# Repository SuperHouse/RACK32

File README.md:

Rack32 ESP32 rack-mount controller with Ethernet
================================================

Copyright 2021 SuperHouse Automation Pty Ltd  www.superhouse.tv

A general purpose control board for rack mount projects, compatible
with the [Open eXtensible Rack System](https://oxrs.io/).

DIY rack-mount projects often require an Ethernet connection, a
status display, power regulation, and other features that are not
specific to the project.

This board fits into a rack-mount case and provides those common
features so they don't have to be recreated every time.

Features:

 * ESP32 microcontroller with WiFi.
 * 10/100Mbps Ethernet.
 * Support for both DIY (12V) PoE and 48V 802.3af PoE.
 * Pluggable terminal block for optional external DC power input.
 * Automotive-grade voltage regulator for harsh electrical environments.
 * 6-way IDC "I2C-Breakout" header for linking to other boards.
 * 8-way IDC "SPI-LCD" header for connection to an LCD.
 * USB-C connector for loading firmware.
 * Auto power source selection between USB-C, PoE, and external DC.
 * I/O header with power, 2 x I2C ports, and second hardware serial port.
 * Micro SD card slot for config files, logs, and media storage.
 * Onboard temperature sensor.
 * Header for front-panel power LED.
 * Can be built with onboard PCB antenna or external WiFi antenna.

More information:

  [www.superhouse.tv/rack32](http://www.superhouse.tv/rack32)

INSTALLATION
------------
The design is saved as an EAGLE project. EAGLE PCB design software is
available from www.cadsoftusa.com free for non-commercial use. To use
this project download it and place the directory containing these files
into the "eagle" directory on your computer. Then open EAGLE and
navigate to the project.

CREDITS
-------
Designed by Jonathan Oxer jon@oxer.com.au

DISTRIBUTION
------------
The specific terms of distribution of this project are governed by the
license referenced below.

LICENSE
-------
Licensed under the TAPR Open Hardware License (www.tapr.org/OHL).
The "license" folder within this repository also contains a copy of
this license in plain text format.

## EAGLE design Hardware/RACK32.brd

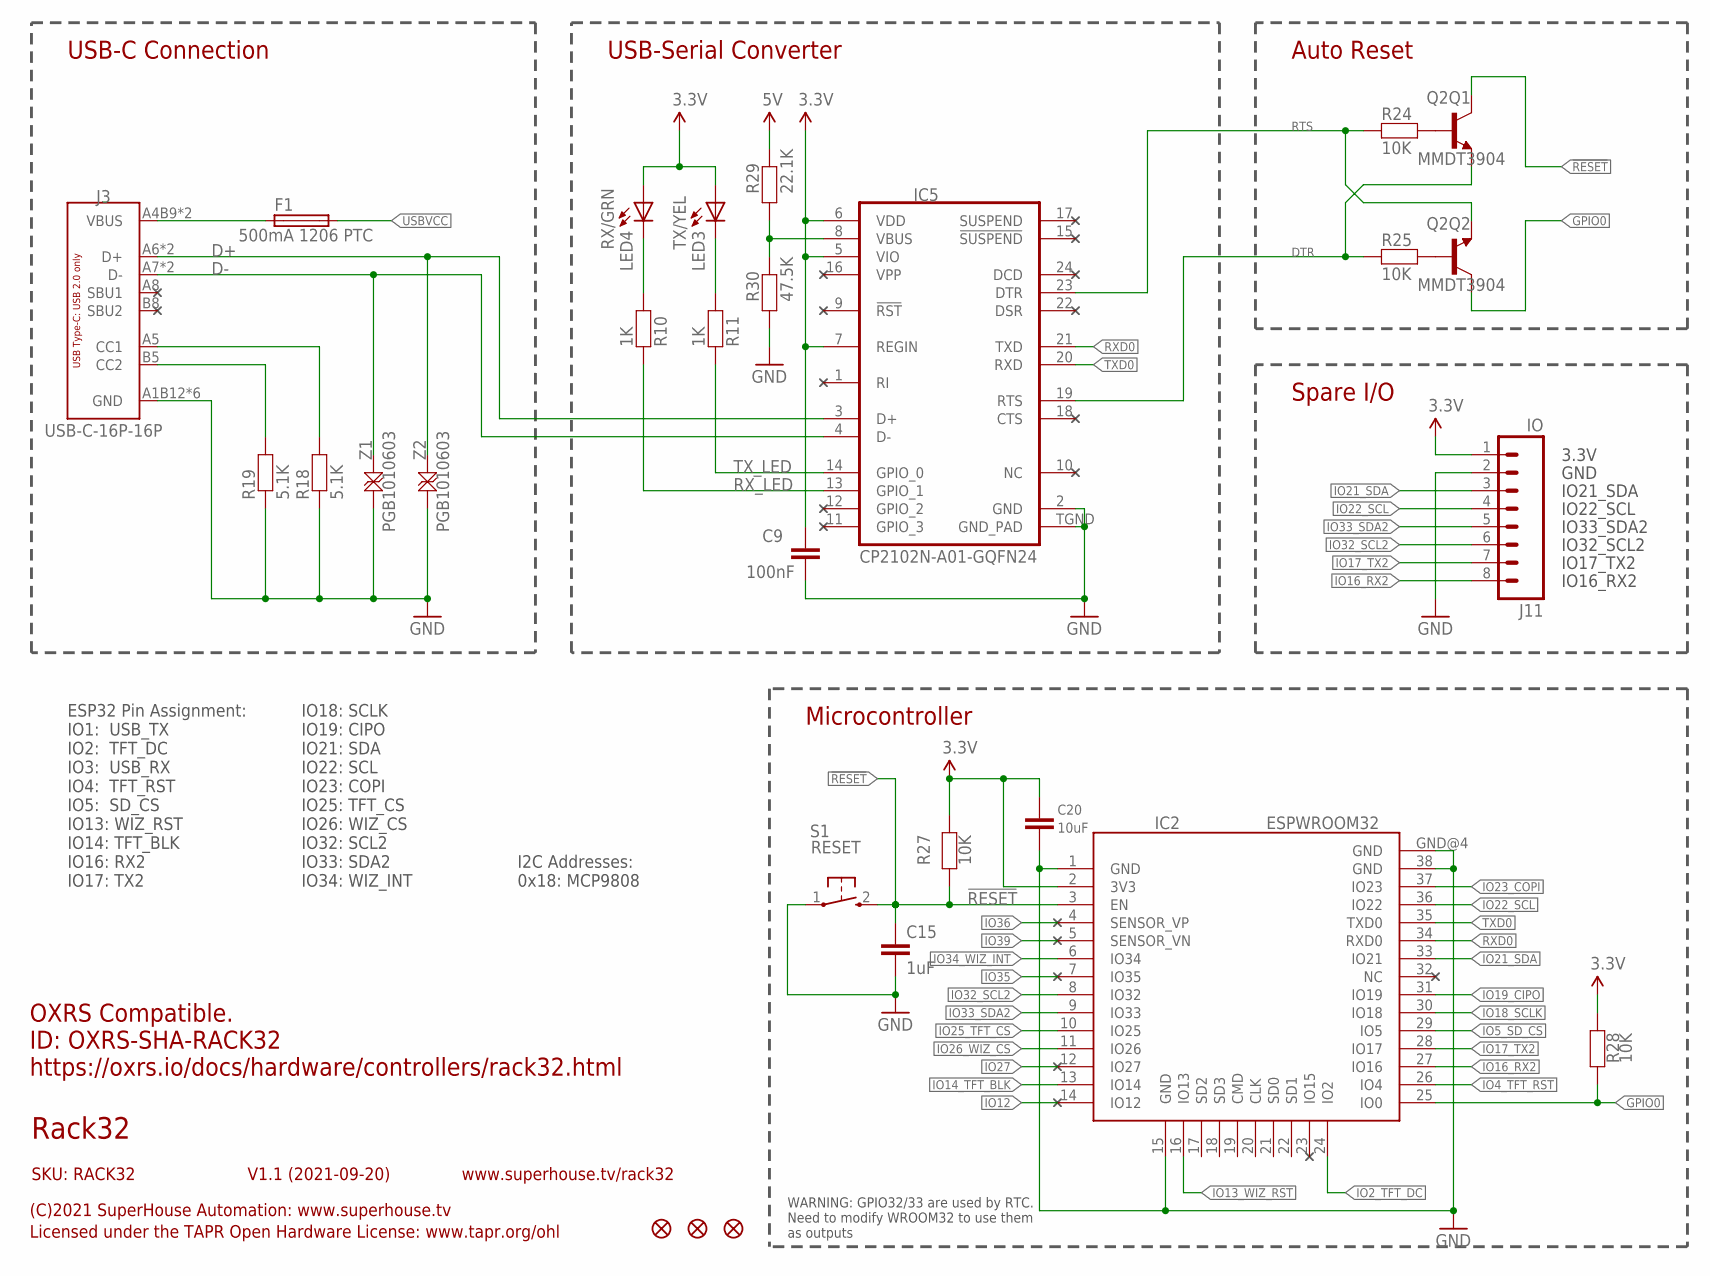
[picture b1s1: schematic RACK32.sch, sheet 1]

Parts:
C9: 100nF; C0603
C15: 1uF; C0603
C20: 10uF; C0805
F1: 500mA 1206 PTC; 1206
FID1, FID2, FID3: FIDUCIAL1X2.5; FIDUCIAL-1X2.5
IC2: ESPWROOM32
IC5: CP2102N-A01-GQFN24; QFN-24
J3: USB-C-16P-16P; USB-C-16P
J11: IO; 1X08
LED3: TX/YEL; LED-0603
LED4: RX/GRN; LED-0603
Q2: MMDT3904; SOT-363
R10, R11: 1K; R0603
R18, R19: 5.1K; R0603
R24, R25, R27, R28: 10K; R0603
R29: 22.1K; R0603
R30: 47.5K; R0603
S1: RESET; TACTILE_SMT_3X4X2
Z1, Z2: PGB1010603; TVS0603

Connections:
3.3V: C9.1, C20.1, IC2.2 (3V3), IC5.5 (VIO), IC5.6 (VDD), IC5.7 (REGIN), J11.1, LED3.A, LED4.A, R27.1, R28.1; also elsewhere on the board
5V: R29.2; also elsewhere on the board
!RESET: C15.1, IC2.3 (EN), Q2.3 (C), R27.2, S1.2 (S); also elsewhere on the board
D+: IC5.3 (D+), J3.A6 (D+), J3.B6 (D+), Z2.2
D-: IC5.4 (D-), J3.A7 (D-), J3.B7 (D-), Z1.2
DTR: IC5.23 (DTR), Q2.1 (E), R24.1
GND: C9.2, C15.2, C20.2, IC2.1 (GND), IC2.15 (GND), IC2.38 (GND), IC2.GND@4 (GND), IC5.2 (GND), IC5.TGND (GND_PAD), J3.A1B12 (GND), J3.A12B1 (GND), J3.FIX1 (GND), J3.FIX2 (GND), J3.FIX3 (GND), J3.FIX4 (GND), J11.2, R18.1, R19.1, R30.1, S1.1, Z1.1, Z2.1; also elsewhere on the board
GPIO0: IC2.25 (IO0), Q2.6 (C), R28.2
IO2_TFT_DC: IC2.24 (IO2); also elsewhere on the board
IO4_TFT_RST: IC2.26 (IO4); also elsewhere on the board
IO5_SD_CS: IC2.29 (IO5); also elsewhere on the board
IO12: IC2.14 (IO12)
IO13_WIZ_RST: IC2.16 (IO13); also elsewhere on the board
IO14_TFT_BLK: IC2.13 (IO14); also elsewhere on the board
IO16_RX2: IC2.27 (IO16), J11.8
IO17_TX2: IC2.28 (IO17), J11.7
IO18_SCLK: IC2.30 (IO18); also elsewhere on the board
IO19_CIPO: IC2.31 (IO19); also elsewhere on the board
IO21_SDA: IC2.33 (IO21), J11.3; also elsewhere on the board
IO22_SCL: IC2.36 (IO22), J11.4; also elsewhere on the board
IO23_COPI: IC2.37 (IO23); also elsewhere on the board
IO25_TFT_CS: IC2.10 (IO25); also elsewhere on the board
IO26_WIZ_CS: IC2.11 (IO26); also elsewhere on the board
IO27: IC2.12 (IO27)
IO32_SCL2: IC2.8 (IO32), J11.6
IO33_SDA2: IC2.9 (IO33), J11.5
IO34_WIZ_INT: IC2.6 (IO34); also elsewhere on the board
IO35: IC2.7 (IO35)
IO36: IC2.4 (SENSOR_VP)
IO39: IC2.5 (SENSOR_VN)
unnamed: Q2.2 (B), R25.2
unnamed: J3.B5 (CC2), R19.2
unnamed: J3.A5 (CC1), R18.2
unnamed: Q2.5 (B), R24.2
unnamed: LED3.C, R11.2
unnamed: LED4.C, R10.2
unnamed: IC5.8 (VBUS), R29.1, R30.2
RTS: IC5.19 (RTS), Q2.4 (E), R25.1
RXD0: IC2.34 (RXD0), IC5.21 (TXD)
RX_LED: IC5.13 (GPIO_1), R10.1
TXD0: IC2.35 (TXD0), IC5.20 (RXD)
TX_LED: IC5.14 (GPIO_0), R11.1
USBVCC: F1.2; also elsewhere on the board
USBVIN: F1.1, J3.A4B9 (VBUS), J3.A9B4 (VBUS)

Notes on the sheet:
USB-C Connection
USB-Serial Converter
Auto Reset
Microcontroller
WARNING: GPIO32/33 are used by RTC. Need to modify WROOM32 to use them as outputs
I2C Addresses: 0x18: MCP9808
ESP32 Pin Assignment: IO1: USB_TX IO2: TFT_DC IO3: USB_RX IO4: TFT_RST IO5: SD_CS IO13: WIZ_RST IO14: TFT_BLK IO16: RX2 IO17: TX2
Rack32
SKU: RACK32
(C)2021 SuperHouse Automation: www.superhouse.tv
Licensed under the TAPR Open Hardware License: www.tapr.org/ohl
www.superhouse.tv/rack32
V1.1 (2021-09-20)
Spare I/O
3.3V
GND
IO21_SDA
IO22_SCL
IO33_SDA2
IO32_SCL2
IO17_TX2
IO16_RX2
OXRS Compatible. ID: OXRS-SHA-RACK32 https://oxrs.io/docs/hardware/controllers/rack32.html
IO18: SCLK IO19: CIPO IO21: SDA IO22: SCL IO23: COPI IO25: TFT_CS IO26: WIZ_CS IO32: SCL2 IO33: SDA2 IO34: WIZ_INT

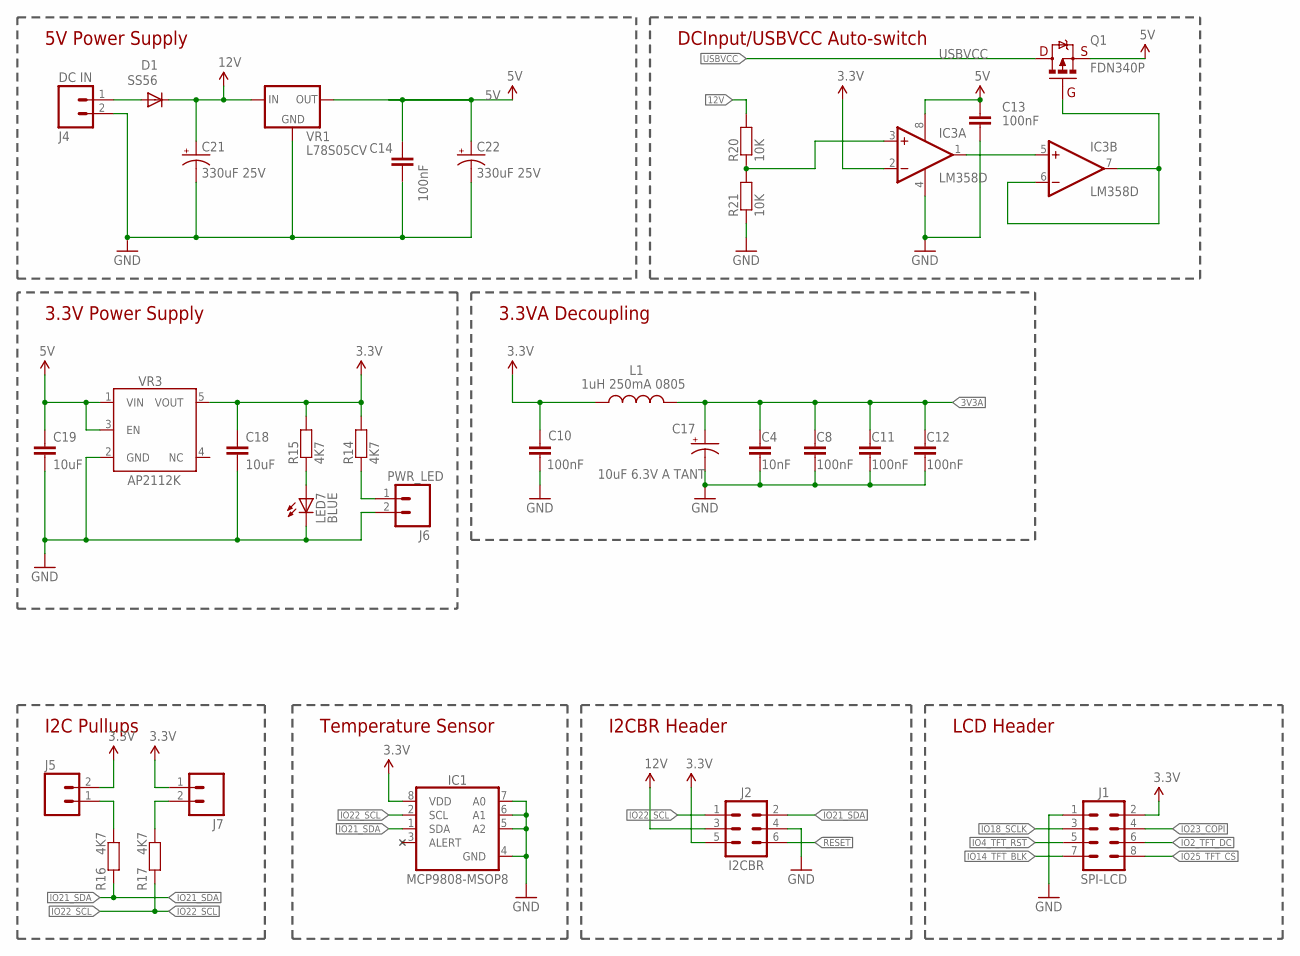
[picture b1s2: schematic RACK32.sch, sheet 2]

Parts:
C4: 10nF; C0603
C8, C10, C11, C12, C13, C14: 100nF; C0603
C17: 10uF 6.3V A TANT; EIA3216
C18, C19: 10uF; C0805
C21, C22: 330uF 25V; PANASONIC_G
D1: SS56; SMA-DIODE
IC1: MCP9808-MSOP8; MSOP-8
IC3: LM358D; SO08
J1: SPI-LCD; 2X04-2.54-SHROUDED
J2: I2CBR; 2X3-2.54-SHROUDED
J4: DC IN; SCREWTERMINAL-3.81MM-HOR-2
J5, J7: M02-PIN-JUMP-Y; 1X02-P-JUMP-Y
J6: PWR_LED; 1X02-P
L1: 1uH 250mA 0805; L2012C
LED7: BLUE; LED-0603
Q1: FDN340P; SOT23-3
R14, R15, R16, R17: 4K7; R0603
R20, R21: 10K; R0603
VR1: L78S05CV; TO220
VR3: AP2112KSOT25; SOT23-5

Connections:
3.3V: C10.1, C18.1, IC1.8 (VDD), IC3.2 (-IN), J1.2, J2.5, J5.2, J7.1, L1.1, R14.2, R15.2, VR3.5 (VOUT); also elsewhere on the board
3V3A: C4.1, C8.1, C11.1, C12.1, C17.A (+), L1.2; also elsewhere on the board
5V: C13.1, C14.1, C19.1, C22.+, IC3.8 (V+), Q1.2 (S), VR1.3 (OUT), VR3.1 (VIN), VR3.3 (EN); also elsewhere on the board
12V: C21.+, D1.C, J2.3, R20.2, VR1.1 (IN); also elsewhere on the board
!RESET: J2.6; also elsewhere on the board
GND: C4.2, C8.2, C10.2, C11.2, C12.2, C13.2, C14.2, C17.C (-), C18.2, C19.2, C21.-, C22.-, IC1.4 (GND), IC1.5 (A2), IC1.6 (A1), IC1.7 (A0), IC3.4 (V-), J1.1, J2.4, J4.2, J6.2, LED7.C, R21.1, VR1.2 (GND), VR1.HEATSINK (GND), VR1.TAB (GND), VR3.2 (GND); also elsewhere on the board
IO2_TFT_DC: J1.6; also elsewhere on the board
IO4_TFT_RST: J1.5; also elsewhere on the board
IO14_TFT_BLK: J1.7; also elsewhere on the board
IO18_SCLK: J1.3; also elsewhere on the board
IO21_SDA: IC1.1 (SDA), J2.2, R16.2; also elsewhere on the board
IO22_SCL: IC1.2 (SCL), J2.1, R17.2; also elsewhere on the board
IO23_COPI: J1.4; also elsewhere on the board
IO25_TFT_CS: J1.8; also elsewhere on the board
unnamed: LED7.A, R15.1
unnamed: J6.1, R14.1
unnamed: J5.1, R16.1
unnamed: J7.2, R17.1
unnamed: IC3.3 (+IN), R20.1, R21.2
unnamed: IC3.6 (-IN), IC3.7 (OUT), Q1.1 (G)
unnamed: IC3.1 (OUT), IC3.5 (+IN)
unnamed: D1.A, J4.1
USBVCC: Q1.3 (D); also elsewhere on the board

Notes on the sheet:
5V Power Supply
DCInput/USBVCC Auto-switch
3.3VA Decoupling
3.3V Power Supply
LCD Header
I2CBR Header
Temperature Sensor
I2C Pullups

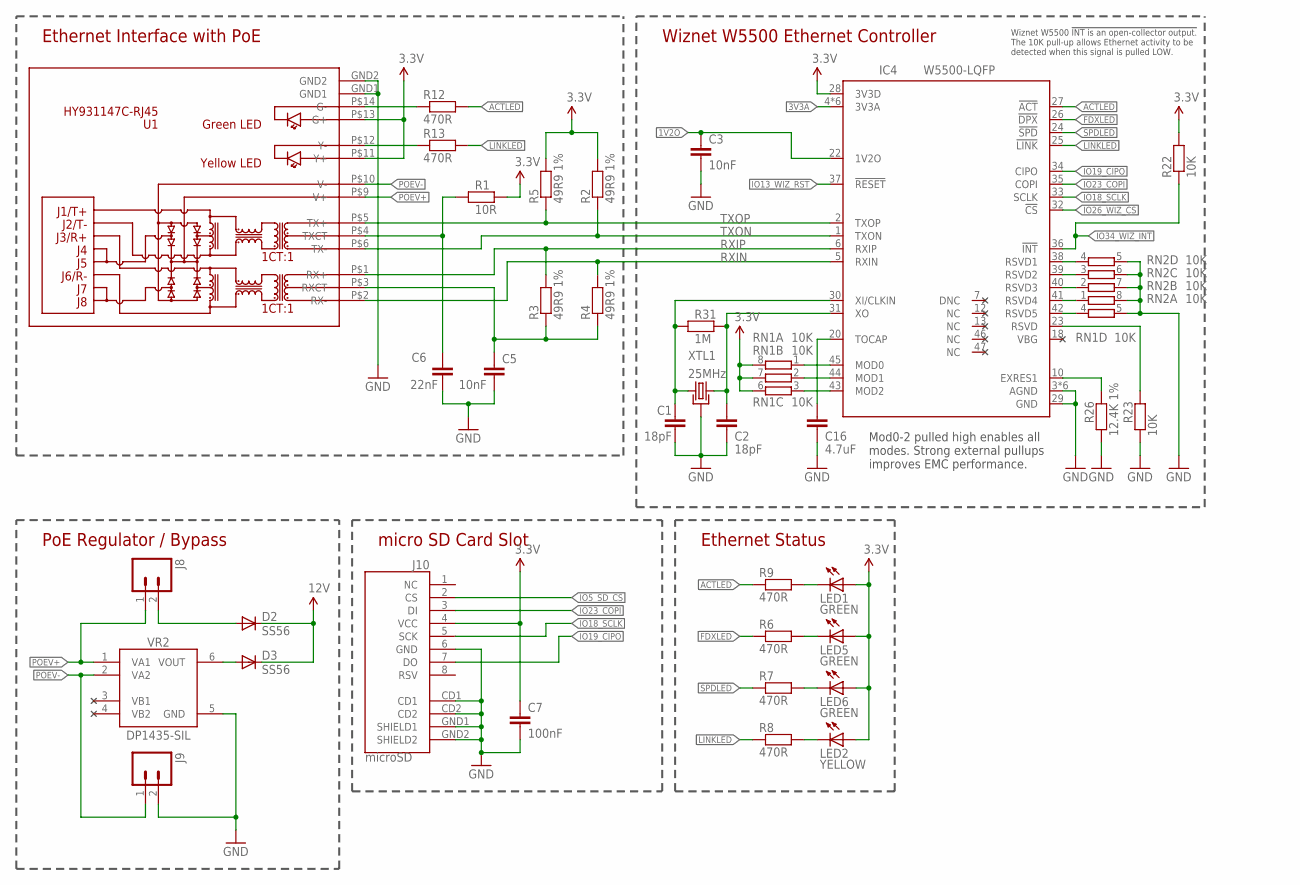
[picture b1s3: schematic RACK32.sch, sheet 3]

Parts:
C1, C2: 18pF; C0603
C3, C5: 10nF; C0603
C6: 22nF; C0603
C7: 100nF; C0603
C16: 4.7uF; C0603
D2, D3: SS56; SMA-DIODE
IC4: W5500-LQFP; LQFP48
J8, J9: M02-PIN-JUMP-Y; 1X02-P-JUMP-Y
J10: microSD; MICRO-SD-SOCKET-PP
LED1, LED5, LED6: GREEN; LED-0603
LED2: YELLOW; LED-0603
R1: 10R; R0603
R2, R3, R4, R5: 49R9 1%; R0603
R6, R7, R8, R9, R12, R13: 470R; R0603
R22, R23: 10K; R0603
R26: 12.4K 1%; R0603
R31: 1M; R0603
RN1, RN2: 10K; CAY16
U1: HY931147C-RJ45; HY931147C
VR2: DP1435-SIL; DP1435
XTL1: 25MHz; CRYSTAL-SMD-3X2

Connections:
1V2O: C3.1, IC4.22 (1V2O)
3.3V: C7.1, IC4.28 (3V3D), J10.4 (VCC), LED1.A, LED2.A, LED5.A, LED6.A, R1.1, R2.2, R5.2, R22.2, RN1.6 (2), RN1.7 (2), RN1.8 (2), U1.P$11 (Y+), U1.P$13 (G+); also elsewhere on the board
3V3A: IC4.4 (3V3A), IC4.8 (3V3A), IC4.11 (3V3A), IC4.15 (3V3A), IC4.17 (3V3A), IC4.21 (3V3A); also elsewhere on the board
12V: D2.C, D3.C; also elsewhere on the board
ACTLED: IC4.27 (!ACT), R9.1, R12.2
FDXLED: IC4.26 (!DPX), R6.1
GND: C1.2, C2.2, C3.2, C5.2, C6.2, C7.2, C16.2, IC4.3 (AGND), IC4.9 (AGND), IC4.14 (AGND), IC4.16 (AGND), IC4.19 (AGND), IC4.29 (GND), IC4.48 (AGND), J9.2, J10.6 (GND), J10.CD1, J10.CD2, J10.GND1 (SHIELD1), J10.GND2 (SHIELD2), R23.2, R26.2, RN1.5 (2), RN2.5 (2), RN2.6 (2), RN2.7 (2), RN2.8 (2), U1.GND1, U1.GND2, VR2.5 (GND), XTL1.2 (GND), XTL1.4 (GND); also elsewhere on the board
IO5_SD_CS: J10.2 (CS); also elsewhere on the board
IO13_WIZ_RST: IC4.37 (!RESET); also elsewhere on the board
IO18_SCLK: IC4.33 (SCLK), J10.5 (SCK); also elsewhere on the board
IO19_CIPO: IC4.34 (CIPO), J10.7 (DO); also elsewhere on the board
IO23_COPI: IC4.35 (COPI), J10.3 (DI); also elsewhere on the board
IO26_WIZ_CS: IC4.32 (!CS); also elsewhere on the board
IO34_WIZ_INT: IC4.36 (!INT), R22.1; also elsewhere on the board
LINKLED: IC4.25 (!LINK), R8.1, R13.2
unnamed: C5.1, R3.1, R4.1, U1.P$3 (RXCT)
unnamed: D2.A, J8.2
unnamed: C2.1, IC4.31 (XO), R31.1, XTL1.3 (2)
unnamed: D3.A, VR2.6 (VOUT)
unnamed: LED6.C, R7.2
unnamed: C1.1, IC4.30 (XI/CLKIN), R31.2, XTL1.1
unnamed: LED2.C, R8.2
unnamed: C16.1, IC4.20 (TOCAP)
unnamed: C6.1, R1.2, U1.P$4 (TXCT)
unnamed: IC4.10 (EXRES1), R26.1
unnamed: IC4.23 (RSVD), R23.1
unnamed: IC4.45 (MOD0), RN1.1
unnamed: IC4.44 (MOD1), RN1.2 (1)
unnamed: IC4.43 (MOD2), RN1.3 (1)
unnamed: IC4.42 (RSVD5), RN1.4 (1)
unnamed: IC4.41 (RSVD4), RN2.1
unnamed: IC4.40 (RSVD3), RN2.2 (1)
unnamed: IC4.39 (RSVD2), RN2.3 (1)
unnamed: IC4.38 (RSVD1), RN2.4 (1)
unnamed: R12.1, U1.P$14 (G-)
unnamed: LED5.C, R6.2
unnamed: LED1.C, R9.2
unnamed: R13.1, U1.P$12 (Y-)
POEV+: J8.1, U1.P$9 (V+), VR2.1 (VA1)
POEV-: J9.1, U1.P$10 (V-), VR2.2 (VA2)
RXIN: IC4.5 (RXIN), R4.2, U1.P$2 (RX-)
RXIP: IC4.6 (RXIP), R3.2, U1.P$1 (RX+)
SPDLED: IC4.24 (!SPD), R7.1
TXON: IC4.1 (TXON), R2.1, U1.P$6 (TX-)
TXOP: IC4.2 (TXOP), R5.1, U1.P$5 (TX+)
VB1: VR2.3 (VB1)
VB2: VR2.4 (VB2)

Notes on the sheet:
micro SD Card Slot
Ethernet Status
Ethernet Interface with PoE
Wiznet W5500 Ethernet Controller
Mod0-2 pulled high enables all modes. Strong external pullups improves EMC performance.
Wiznet W5500 !INT is an open-collector output. The 10K pull-up allows Ethernet activity to be detected when this signal is pulled LOW.
PoE Regulator / Bypass

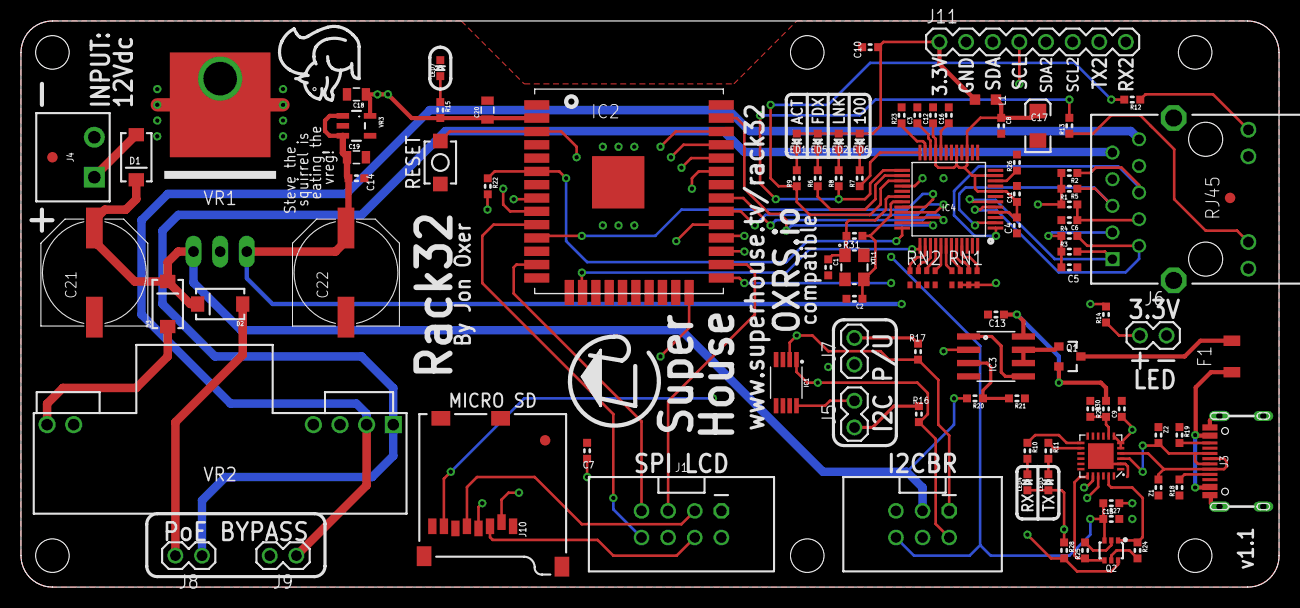
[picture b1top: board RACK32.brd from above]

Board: 4 copper layers, 120.0 x 54.0 mm, 96 parts (0 on the bottom side), 83 nets.

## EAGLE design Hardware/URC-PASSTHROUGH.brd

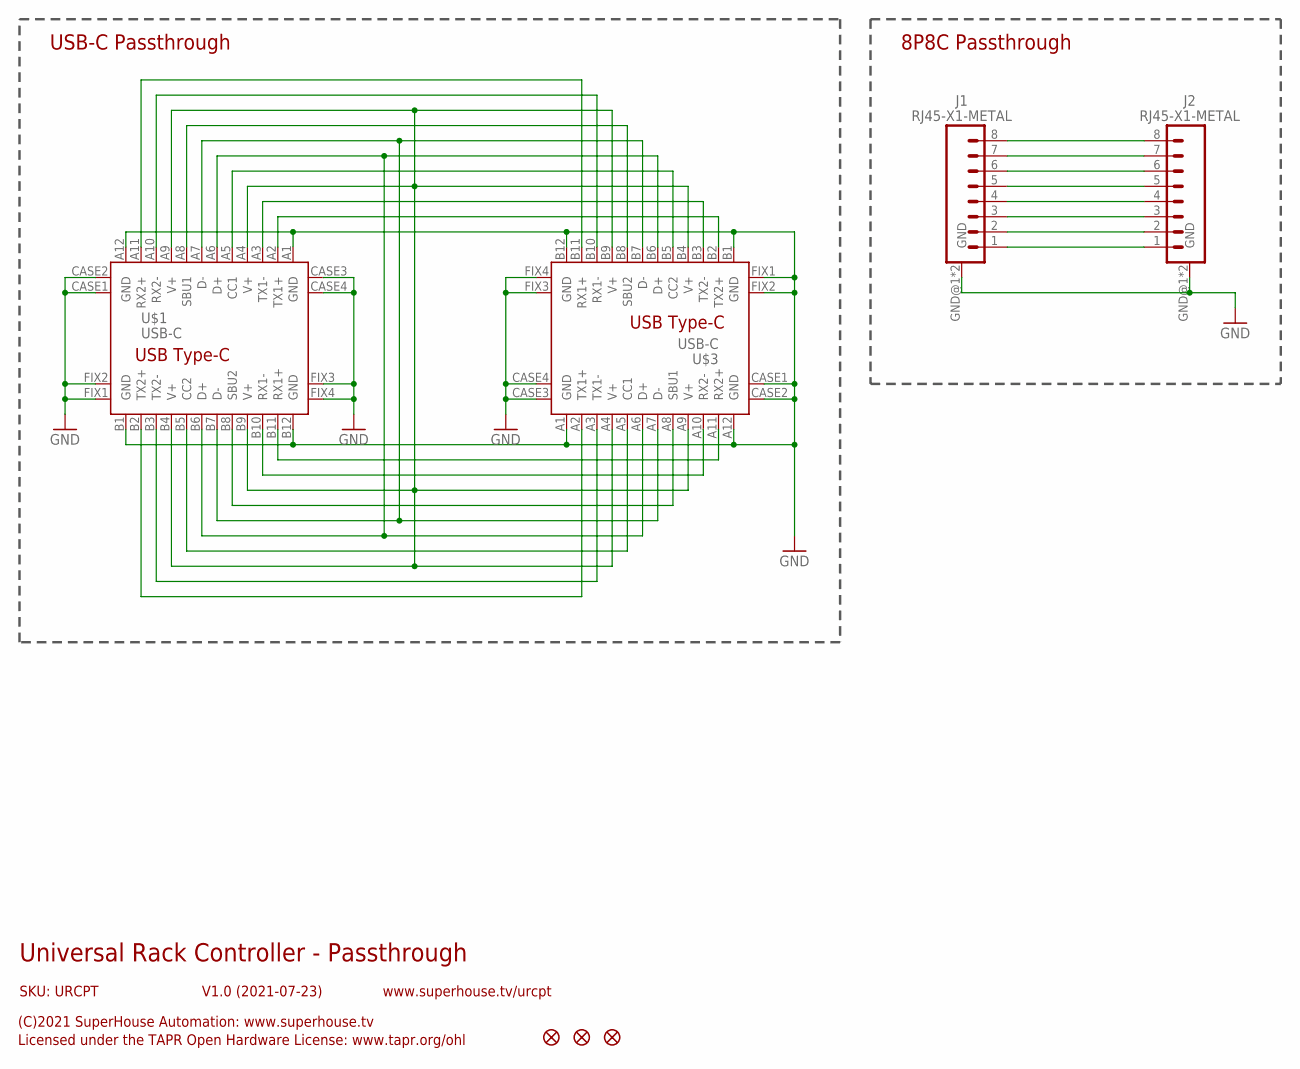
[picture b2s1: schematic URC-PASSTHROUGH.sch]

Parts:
FID1, FID2, FID3: FIDUCIAL1X2.5; FIDUCIAL-1X2.5
J1, J2: RJ45-X1-METAL; RJ45-1X1
U$1, U$3: USB-C; USB-C-U52A

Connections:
GND: J1.GND@1 (GND), J1.GND@2 (GND), J2.GND@1 (GND), J2.GND@2 (GND), U$1.A1 (GND), U$1.A12 (GND), U$1.B1 (GND), U$1.B12 (GND), U$1.CASE1 (GND), U$1.CASE2 (GND), U$1.CASE3 (GND), U$1.CASE4 (GND), U$1.FIX1 (GND), U$1.FIX2 (GND), U$1.FIX3 (GND), U$1.FIX4 (GND), U$3.A1 (GND), U$3.A12 (GND), U$3.B1 (GND), U$3.B12 (GND), U$3.CASE1 (GND), U$3.CASE2 (GND), U$3.CASE3 (GND), U$3.CASE4 (GND), U$3.FIX1 (GND), U$3.FIX2 (GND), U$3.FIX3 (GND), U$3.FIX4 (GND)
unnamed: J1.1, J2.1
unnamed: J1.2, J2.2
unnamed: J1.3, J2.3
unnamed: J1.4, J2.4
unnamed: J1.5, J2.5
unnamed: J1.6, J2.6
unnamed: J1.7, J2.7
unnamed: J1.8, J2.8
unnamed: U$1.A2 (TX1+), U$3.B2 (TX2+)
unnamed: U$1.A3 (TX1-), U$3.B3 (TX2-)
unnamed: U$1.A8 (SBU1), U$3.B8 (SBU2)
unnamed: U$1.A5 (CC1), U$3.B5 (CC2)
unnamed: U$1.A6 (D+), U$1.B6 (D+), U$3.A6 (D+), U$3.B6 (D+)
unnamed: U$1.A7 (D-), U$1.B7 (D-), U$3.A7 (D-), U$3.B7 (D-)
unnamed: U$1.A10 (RX2-), U$3.B10 (RX1-)
unnamed: U$1.A11 (RX2+), U$3.B11 (RX1+)
unnamed: U$1.B11 (RX1+), U$3.A11 (RX2+)
unnamed: U$1.B10 (RX1-), U$3.A10 (RX2-)
unnamed: U$1.A4 (V+), U$1.A9 (V+), U$1.B4 (V+), U$1.B9 (V+), U$3.A4 (V+), U$3.A9 (V+), U$3.B4 (V+), U$3.B9 (V+)
unnamed: U$1.B8 (SBU2), U$3.A8 (SBU1)
unnamed: U$1.B5 (CC2), U$3.A5 (CC1)
unnamed: U$1.B3 (TX2-), U$3.A3 (TX1-)
unnamed: U$1.B2 (TX2+), U$3.A2 (TX1+)

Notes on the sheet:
USB-C Passthrough
Universal Rack Controller - Passthrough
SKU: URCPT
(C)2021 SuperHouse Automation: www.superhouse.tv
Licensed under the TAPR Open Hardware License: www.tapr.org/ohl
www.superhouse.tv/urcpt
V1.0 (2021-07-23)
8P8C Passthrough

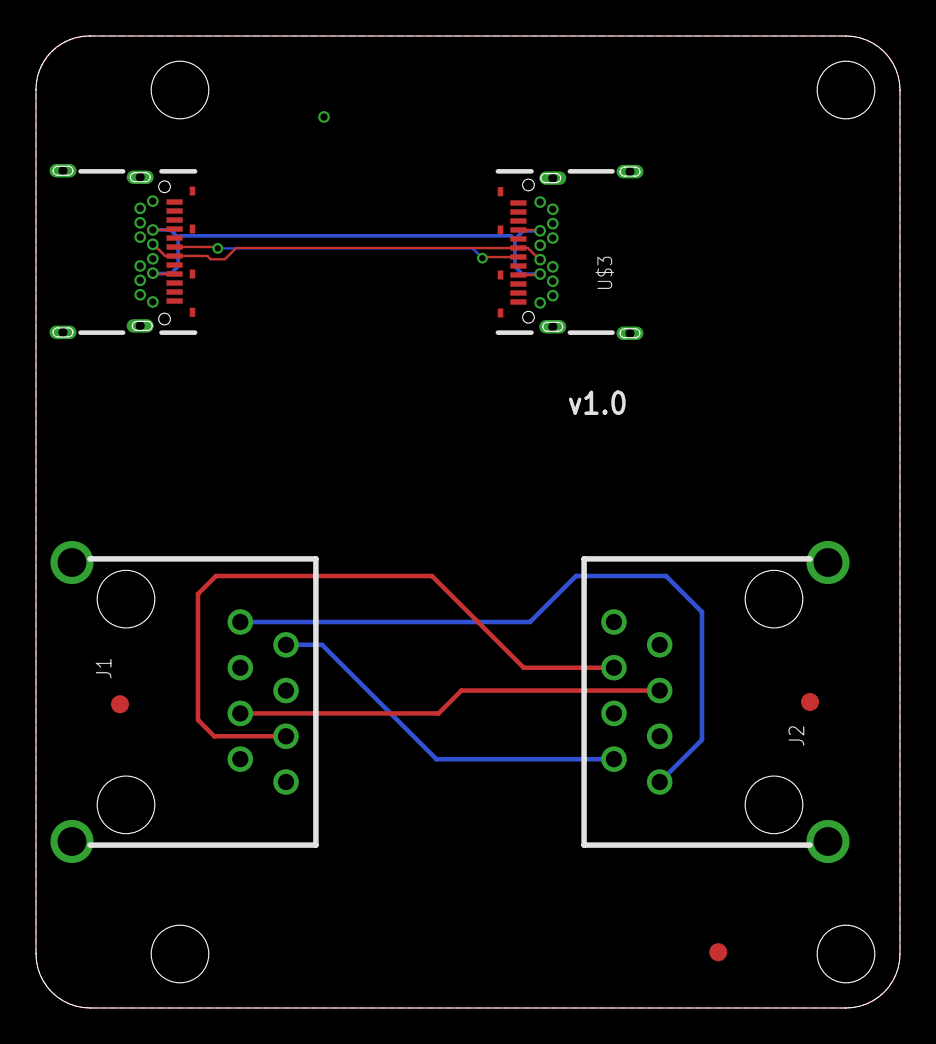
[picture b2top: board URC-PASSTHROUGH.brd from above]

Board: 4 copper layers, 48.0 x 54.0 mm, 7 parts (0 on the bottom side), 24 nets.

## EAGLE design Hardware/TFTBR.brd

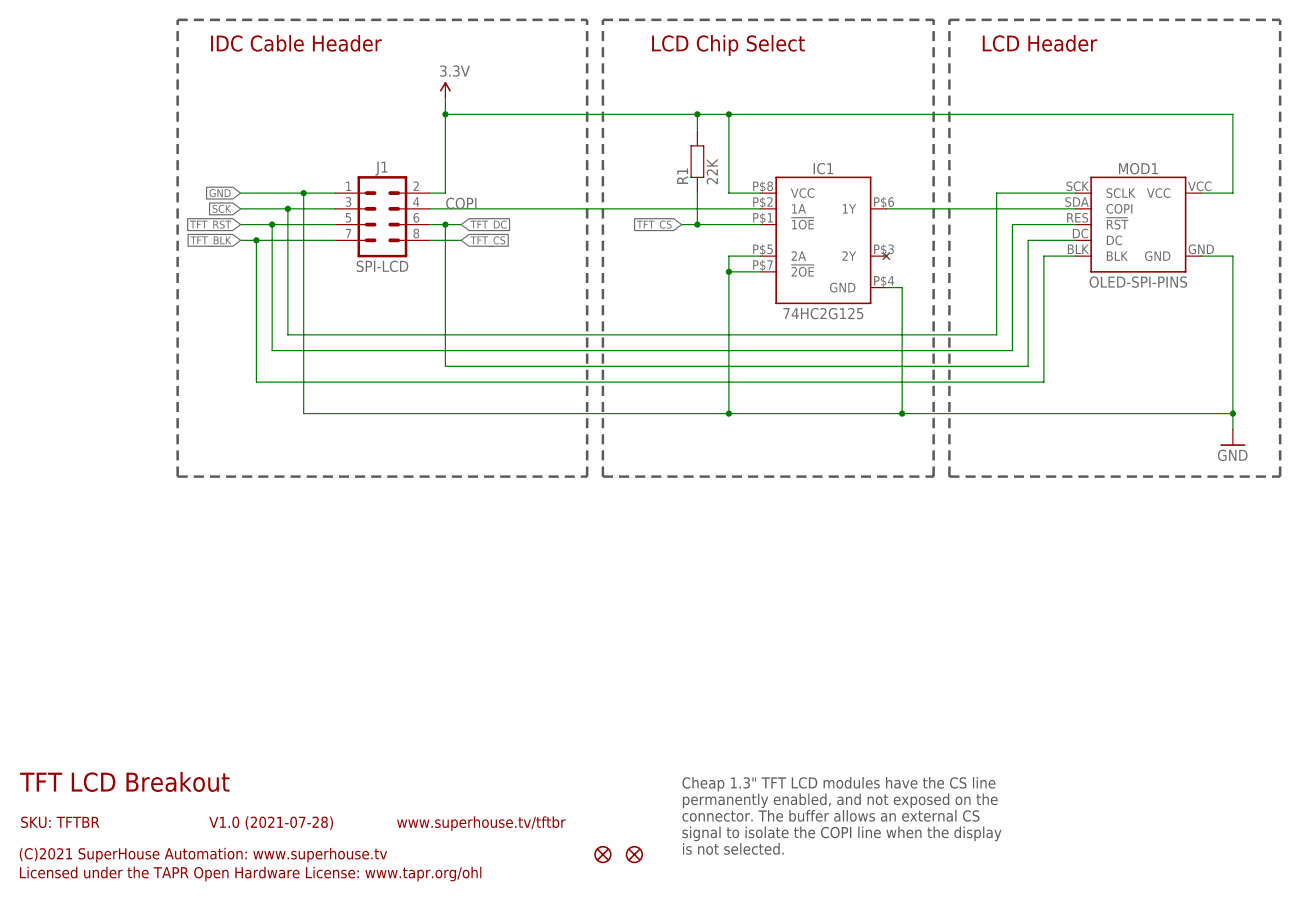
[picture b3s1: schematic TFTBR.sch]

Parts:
FID1, FID2: FIDUCIAL1X2.5; FIDUCIAL-1X2.5
IC1: 74HC2G125
J1: SPI-LCD; 2X04-2.54-SHROUDED
MOD1: OLED-SPI-PINS; OLED-240X240-1.3
R1: 22K; R0603

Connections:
3.3V: IC1.P$8 (VCC), J1.2, MOD1.VCC, R1.2
COPI: IC1.P$2 (1A), J1.4
GND: IC1.P$4 (GND), IC1.P$5 (2A), IC1.P$7 (!2OE), J1.1, MOD1.GND
unnamed: IC1.P$6 (1Y), MOD1.SDA (COPI)
SCK: J1.3, MOD1.SCK (SCLK)
TFT_BLK: J1.7, MOD1.BLK
TFT_CS: IC1.P$1 (!1OE), J1.8, R1.1
TFT_DC: J1.6, MOD1.DC
TFT_RST: J1.5, MOD1.RES (!RST)

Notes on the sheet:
TFT LCD Breakout
SKU: TFTBR
(C)2021 SuperHouse Automation: www.superhouse.tv
Licensed under the TAPR Open Hardware License: www.tapr.org/ohl
www.superhouse.tv/tftbr
V1.0 (2021-07-28)
IDC Cable Header
LCD Chip Select
LCD Header
Cheap 1.3" TFT LCD modules have the CS line permanently enabled, and not exposed on the connector. The buffer allows an external CS signal to isolate the COPI line when the display is not selected.

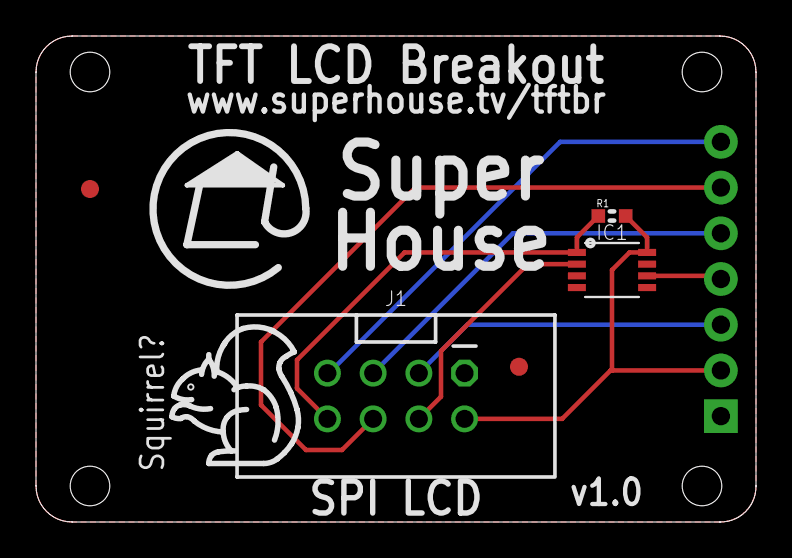
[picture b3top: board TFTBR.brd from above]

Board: 2 copper layers, 40.0 x 27.0 mm, 6 parts (1 on the bottom side), 9 nets.

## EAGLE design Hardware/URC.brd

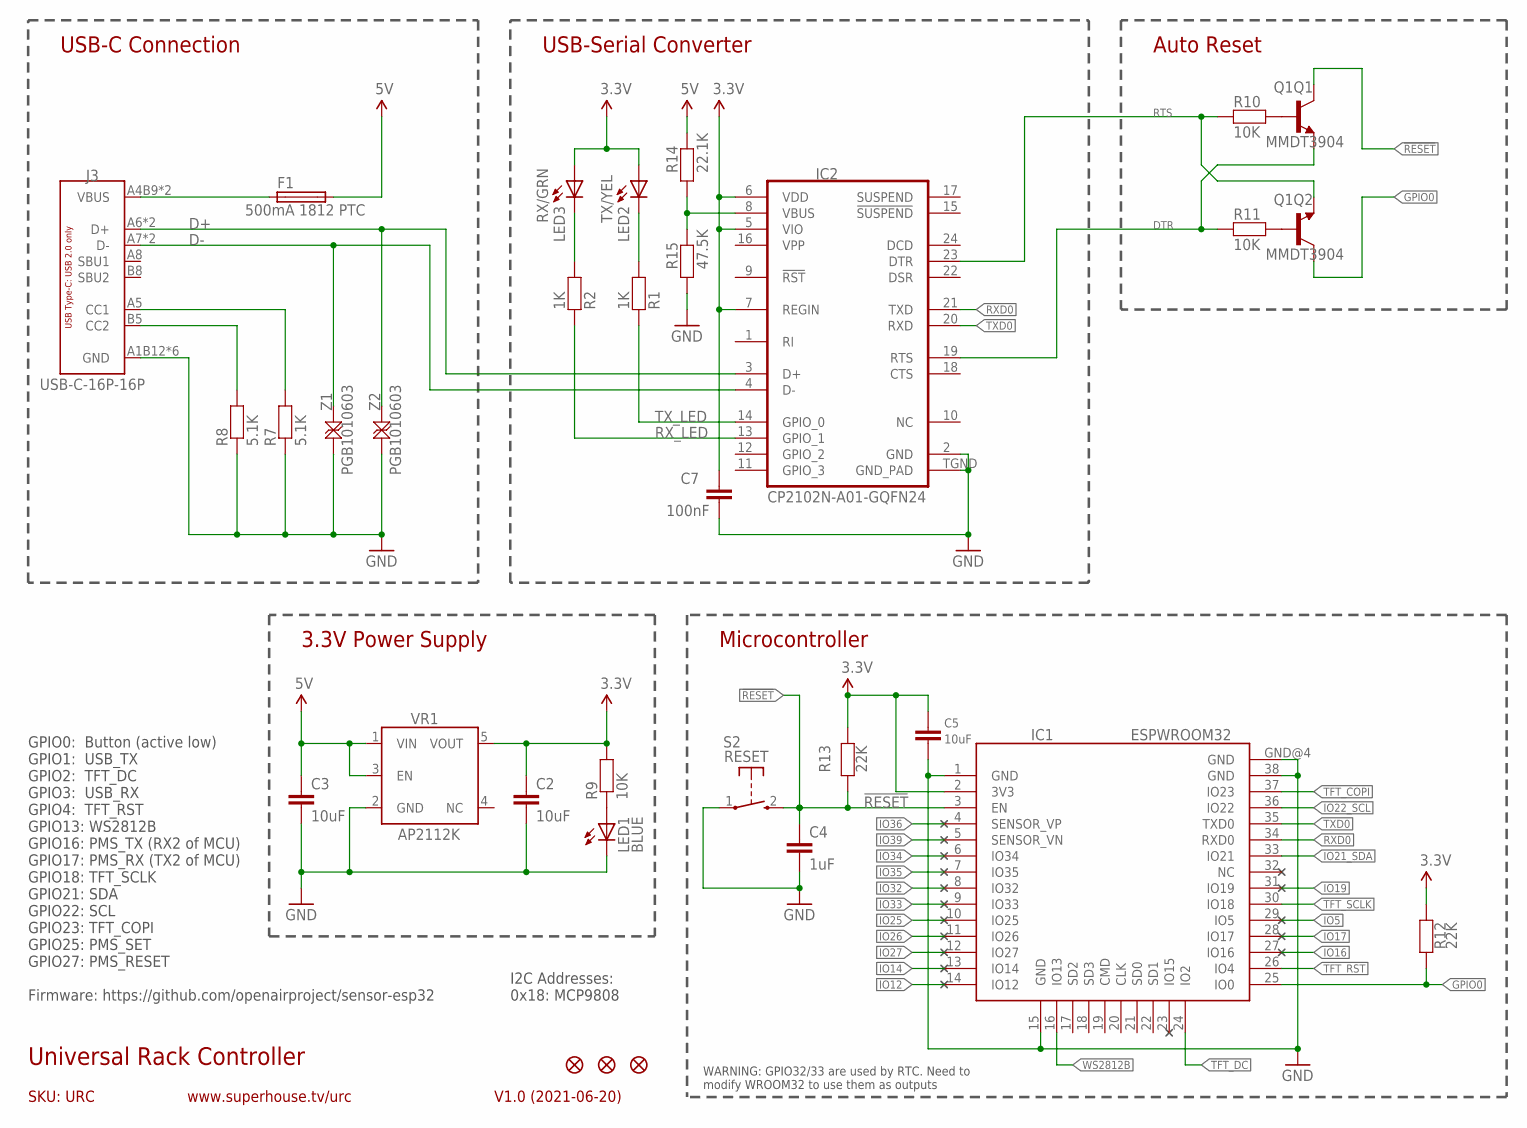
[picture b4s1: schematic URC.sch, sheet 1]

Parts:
C2, C3, C5: 10uF; C0805
C4: 1uF; C0603
C7: 100nF; C0603
F1: 500mA 1812 PTC; 1812
IC1: ESPWROOM32
IC2: CP2102N-A01-GQFN24; QFN-24
J3: USB-C-16P-16P; USB-C-16P
LED1: BLUE; LED-0603
LED2: TX/YEL; LED-0603
LED3: RX/GRN; LED-0603
Q1: MMDT3904; SOT-363
R1, R2: 1K; R0603
R7, R8: 5.1K; R0603
R9, R10, R11: 10K; R0603
R12, R13: 22K; R0603
R14: 22.1K; R0603
R15: 47.5K; R0603
S2: RESET; TACTILE_SMT_3X4X2
U$23, U$24, U$25: FIDUCIAL1X2; FIDUCIAL-1X2
VR1: AP2112KSOT25; SOT23-5
Z1, Z2: PGB1010603; TVS0603

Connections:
3.3V: C2.1, C5.1, C7.1, IC1.2 (3V3), IC2.5 (VIO), IC2.6 (VDD), IC2.7 (REGIN), LED2.A, LED3.A, R9.2, R12.1, R13.1, VR1.5 (VOUT); also elsewhere on the board
5V: C3.1, F1.2, R14.2, VR1.1 (VIN), VR1.3 (EN)
!RESET: C4.1, IC1.3 (EN), Q1.3 (C), R13.2, S2.2 (S)
D+: IC2.3 (D+), J3.A6 (D+), J3.B6 (D+), Z2.2
D-: IC2.4 (D-), J3.A7 (D-), J3.B7 (D-), Z1.2
DTR: IC2.23 (DTR), Q1.1 (E), R10.1
GND: C2.2, C3.2, C4.2, C5.2, C7.2, IC1.1 (GND), IC1.15 (GND), IC1.38 (GND), IC1.GND@4 (GND), IC2.2 (GND), IC2.TGND (GND_PAD), J3.A1B12 (GND), J3.A12B1 (GND), J3.FIX1 (GND), J3.FIX2 (GND), J3.FIX3 (GND), J3.FIX4 (GND), LED1.C, R7.1, R8.1, R15.1, S2.1, VR1.2 (GND), Z1.1, Z2.1; also elsewhere on the board
GPIO0: IC1.25 (IO0), Q1.6 (C), R12.2
IO5: IC1.29 (IO5)
IO12: IC1.14 (IO12)
IO14: IC1.13 (IO14)
IO16: IC1.27 (IO16)
IO17: IC1.28 (IO17)
IO19: IC1.31 (IO19)
IO21_SDA: IC1.33 (IO21); also elsewhere on the board
IO22_SCL: IC1.36 (IO22); also elsewhere on the board
IO25: IC1.10 (IO25)
IO26: IC1.11 (IO26)
IO27: IC1.12 (IO27)
IO32: IC1.8 (IO32)
IO33: IC1.9 (IO33)
IO34: IC1.6 (IO34)
IO35: IC1.7 (IO35)
IO36: IC1.4 (SENSOR_VP)
IO39: IC1.5 (SENSOR_VN)
unnamed: LED1.A, R9.1
unnamed: LED3.C, R2.2
unnamed: Q1.5 (B), R10.2
unnamed: Q1.2 (B), R11.2
unnamed: J3.B5 (CC2), R8.2
unnamed: J3.A5 (CC1), R7.2
unnamed: LED2.C, R1.2
unnamed: IC2.8 (VBUS), R14.1, R15.2
RTS: IC2.19 (RTS), Q1.4 (E), R11.1
RXD0: IC1.34 (RXD0), IC2.21 (TXD)
RX_LED: IC2.13 (GPIO_1), R2.1
TFT_COPI: IC1.37 (IO23); also elsewhere on the board
TFT_DC: IC1.24 (IO2); also elsewhere on the board
TFT_RST: IC1.26 (IO4); also elsewhere on the board
TFT_SCLK: IC1.30 (IO18); also elsewhere on the board
TXD0: IC1.35 (TXD0), IC2.20 (RXD)
TX_LED: IC2.14 (GPIO_0), R1.1
VIN: F1.1, J3.A4B9 (VBUS), J3.A9B4 (VBUS)
WS2812B: IC1.16 (IO13)

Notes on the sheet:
SKU: URC
Universal Rack Controller
V1.0 (2021-06-20)
www.superhouse.tv/urc
USB-C Connection
USB-Serial Converter
Auto Reset
3.3V Power Supply
Microcontroller
WARNING: GPIO32/33 are used by RTC. Need to modify WROOM32 to use them as outputs
I2C Addresses: 0x18: MCP9808
GPIO0: Button (active low) GPIO1: USB_TX GPIO2: TFT_DC GPIO3: USB_RX GPIO4: TFT_RST GPIO13: WS2812B GPIO16: PMS_TX (RX2 of MCU) GPIO17: PMS_RX (TX2 of MCU) GPIO18: TFT_SCLK GPIO21: SDA GPIO22: SCL GPIO23: TFT_COPI GPIO25: PMS_SET GPIO27: PMS_RESET Firmware: https://github.com/openairproject/sensor-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

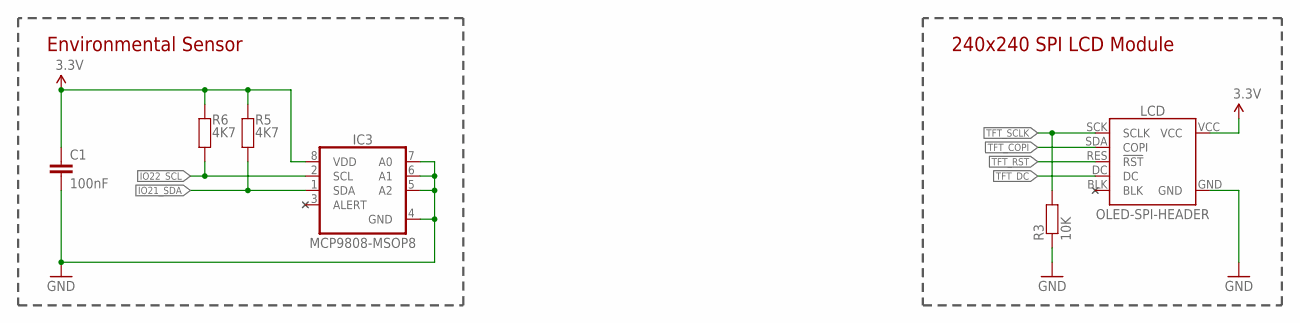
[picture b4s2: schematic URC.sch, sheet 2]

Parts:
C1: 100nF; C0603
IC3: MCP9808-MSOP8; MSOP-8
LCD: OLED-SPI-HEADER; OLED-240X240-1.3-HEADER
R3: 10K; R0603
R5, R6: 4K7; R0603

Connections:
3.3V: C1.1, IC3.8 (VDD), LCD.VCC, R5.2, R6.2; also elsewhere on the board
GND: C1.2, IC3.4 (GND), IC3.5 (A2), IC3.6 (A1), IC3.7 (A0), LCD.GND, R3.1; also elsewhere on the board
IO21_SDA: IC3.1 (SDA), R5.1; also elsewhere on the board
IO22_SCL: IC3.2 (SCL), R6.1; also elsewhere on the board
TFT_COPI: LCD.SDA (COPI); also elsewhere on the board
TFT_DC: LCD.DC; also elsewhere on the board
TFT_RST: LCD.RES (!RST); also elsewhere on the board
TFT_SCLK: LCD.SCK (SCLK), R3.2; also elsewhere on the board

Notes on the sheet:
Environmental Sensor
240x240 SPI LCD Module

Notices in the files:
Hardware/RACK32.brd:
Copyright 2021 SuperHouse Automation P/L
Open Hardware License
Hardware/URC.brd:
(C)2020 SuperHouse
License: tapr.org/OHL
parts and their libraries:
freetronics-original: Licensing: CC v3.0 Share-Alike You are welcome to use this library for commercial purposes.
